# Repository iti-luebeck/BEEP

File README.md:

BEEP
====

BEEP is a small mobile robot build for education purposes.

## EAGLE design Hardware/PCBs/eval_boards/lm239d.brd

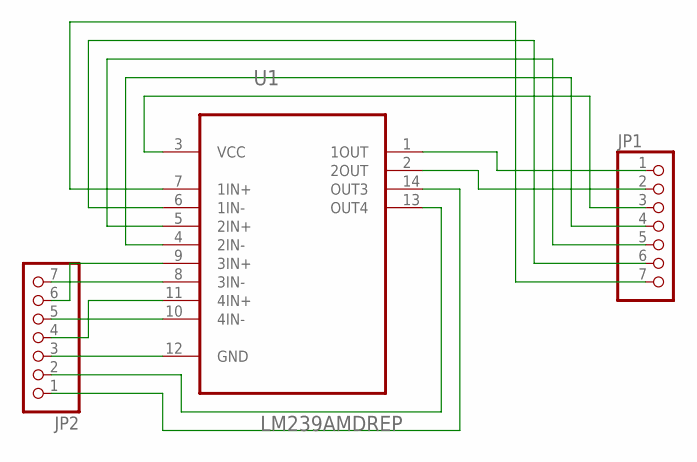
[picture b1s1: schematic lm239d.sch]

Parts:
JP1, JP2: PINHD-1X7; 1X07
U1: LM239AMDREP; SOIC127P600X175-14N

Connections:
unnamed: JP1.1, U1.1 (1OUT)
unnamed: JP1.2, U1.2 (2OUT)
unnamed: JP1.3, U1.3 (VCC)
unnamed: JP1.4, U1.4 (2IN-)
unnamed: JP1.5, U1.5 (2IN+)
unnamed: JP1.6, U1.6 (1IN-)
unnamed: JP1.7, U1.7 (1IN+)
unnamed: JP2.7, U1.8 (3IN-)
unnamed: JP2.6, U1.9 (3IN+)
unnamed: JP2.4, U1.11 (4IN+)
unnamed: JP2.5, U1.10 (4IN-)
unnamed: JP2.3, U1.12 (GND)
unnamed: JP2.2, U1.13 (OUT4)
unnamed: JP2.1, U1.14 (OUT3)

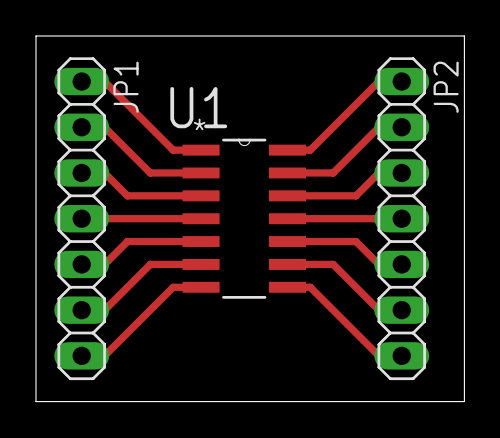
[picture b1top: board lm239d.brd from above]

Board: 2 copper layers, 23.8 x 20.3 mm, 3 parts (0 on the bottom side), 14 nets.

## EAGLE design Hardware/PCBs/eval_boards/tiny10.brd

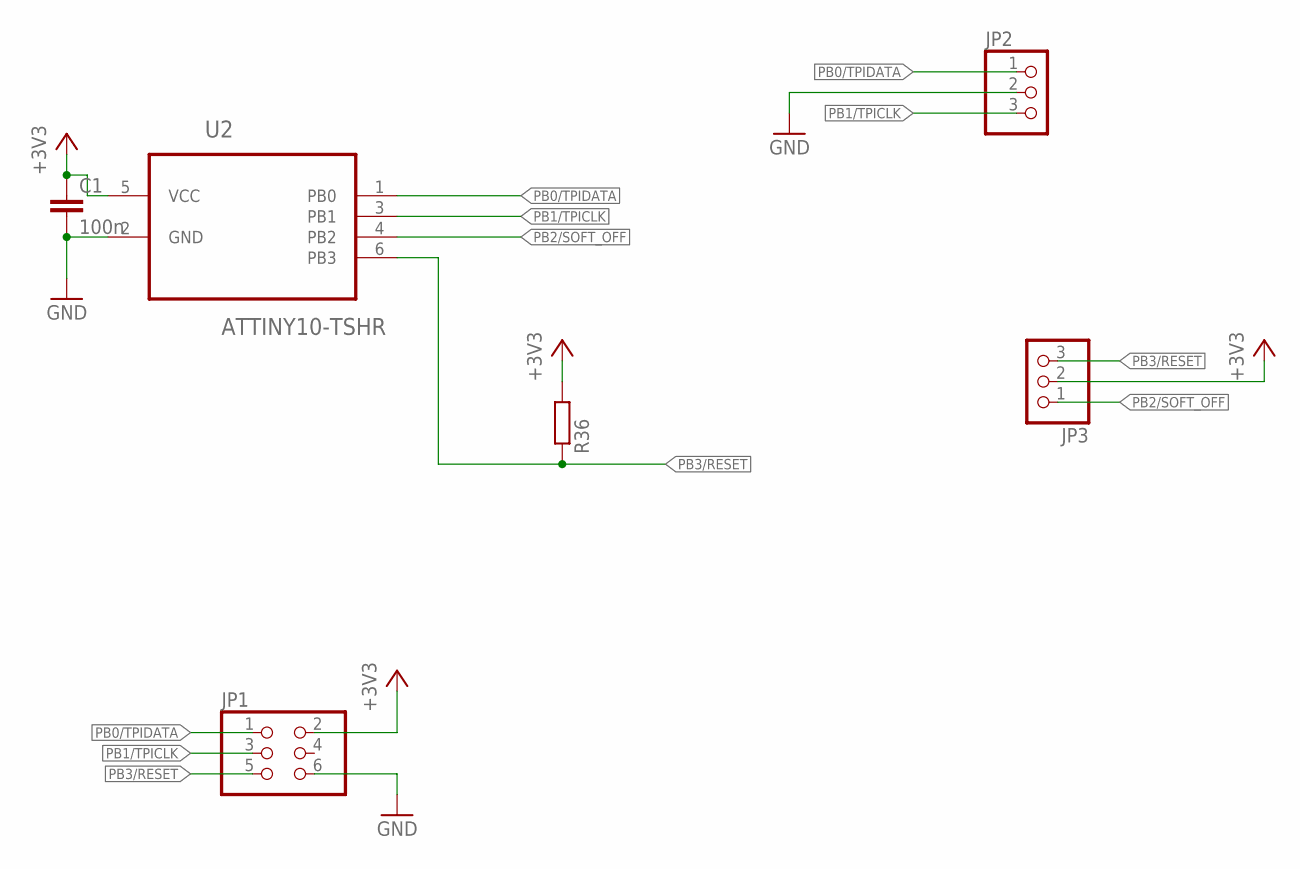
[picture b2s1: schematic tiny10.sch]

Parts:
C1: 100n; C0603
JP1: PINHD-2X3; 2X03
JP2, JP3: PINHD-1X3; 1X03
R36: R-EU_M0805; M0805
U2: ATTINY10-TSHR; SOT95P280X145-6N

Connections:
+3V3: C1.1, JP1.2, JP3.2, R36.2, U2.5 (VCC)
GND: C1.2, JP1.6, JP2.2, U2.2 (GND)
PB0/TPIDATA: JP1.1, JP2.1, U2.1 (PB0)
PB1/TPICLK: JP1.3, JP2.3, U2.3 (PB1)
PB2/SOFT_OFF: JP3.1, U2.4 (PB2)
PB3/RESET: JP1.5, JP3.3, R36.1, U2.6 (PB3)

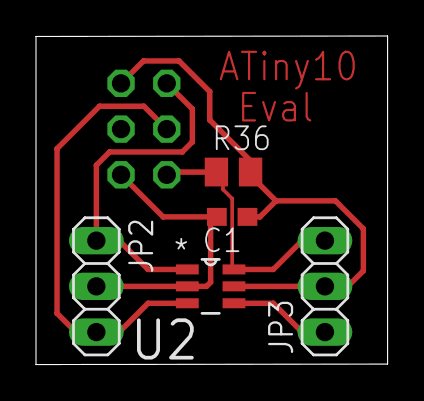
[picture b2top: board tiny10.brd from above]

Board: 2 copper layers, 19.5 x 18.3 mm, 6 parts (1 on the bottom side), 6 nets.

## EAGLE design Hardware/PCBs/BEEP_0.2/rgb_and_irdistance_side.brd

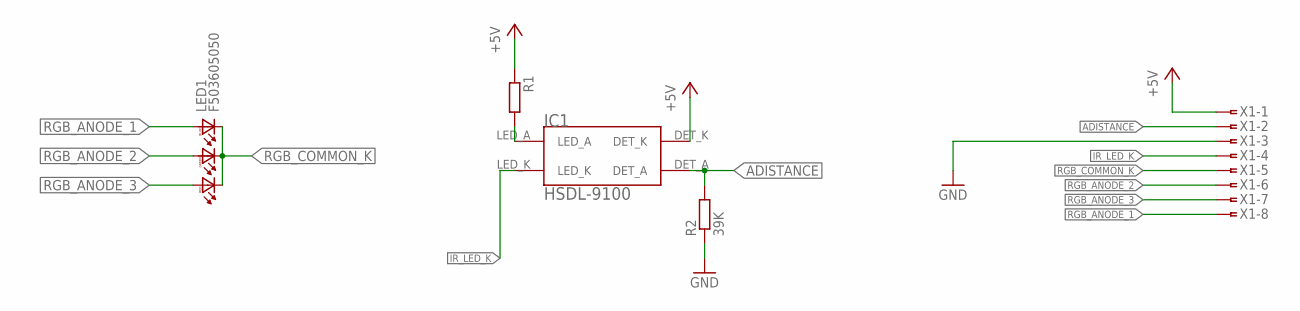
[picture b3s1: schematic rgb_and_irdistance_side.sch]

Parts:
IC1: HSDL-9100
LED1: F503605050; 5050LED
R1: R-EU_M0805; M0805
R2: 39K; M0805
X1: FTOP-8

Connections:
+5V: IC1.DET_K, R1.1, X1.1
ADISTANCE: IC1.DET_A, R2.2, X1.2
GND: R2.1, X1.3
IR_LED_K: IC1.LED_K, X1.4
unnamed: IC1.LED_A, R1.2
RGB_ANODE_1: LED1.B1 (BA), X1.8
RGB_ANODE_2: LED1.G1 (GA), X1.6
RGB_ANODE_3: LED1.R1 (RA), X1.7
RGB_COMMON_K: LED1.B2 (BC), LED1.G2 (GC), LED1.R2 (RC), X1.5

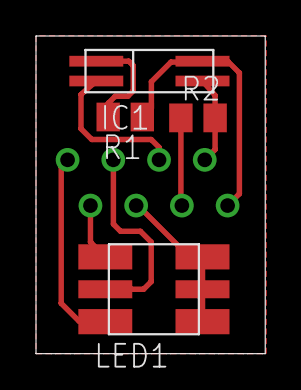
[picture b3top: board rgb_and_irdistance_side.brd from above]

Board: 2 copper layers, 12.7 x 17.7 mm, 5 parts (1 on the bottom side), 9 nets.

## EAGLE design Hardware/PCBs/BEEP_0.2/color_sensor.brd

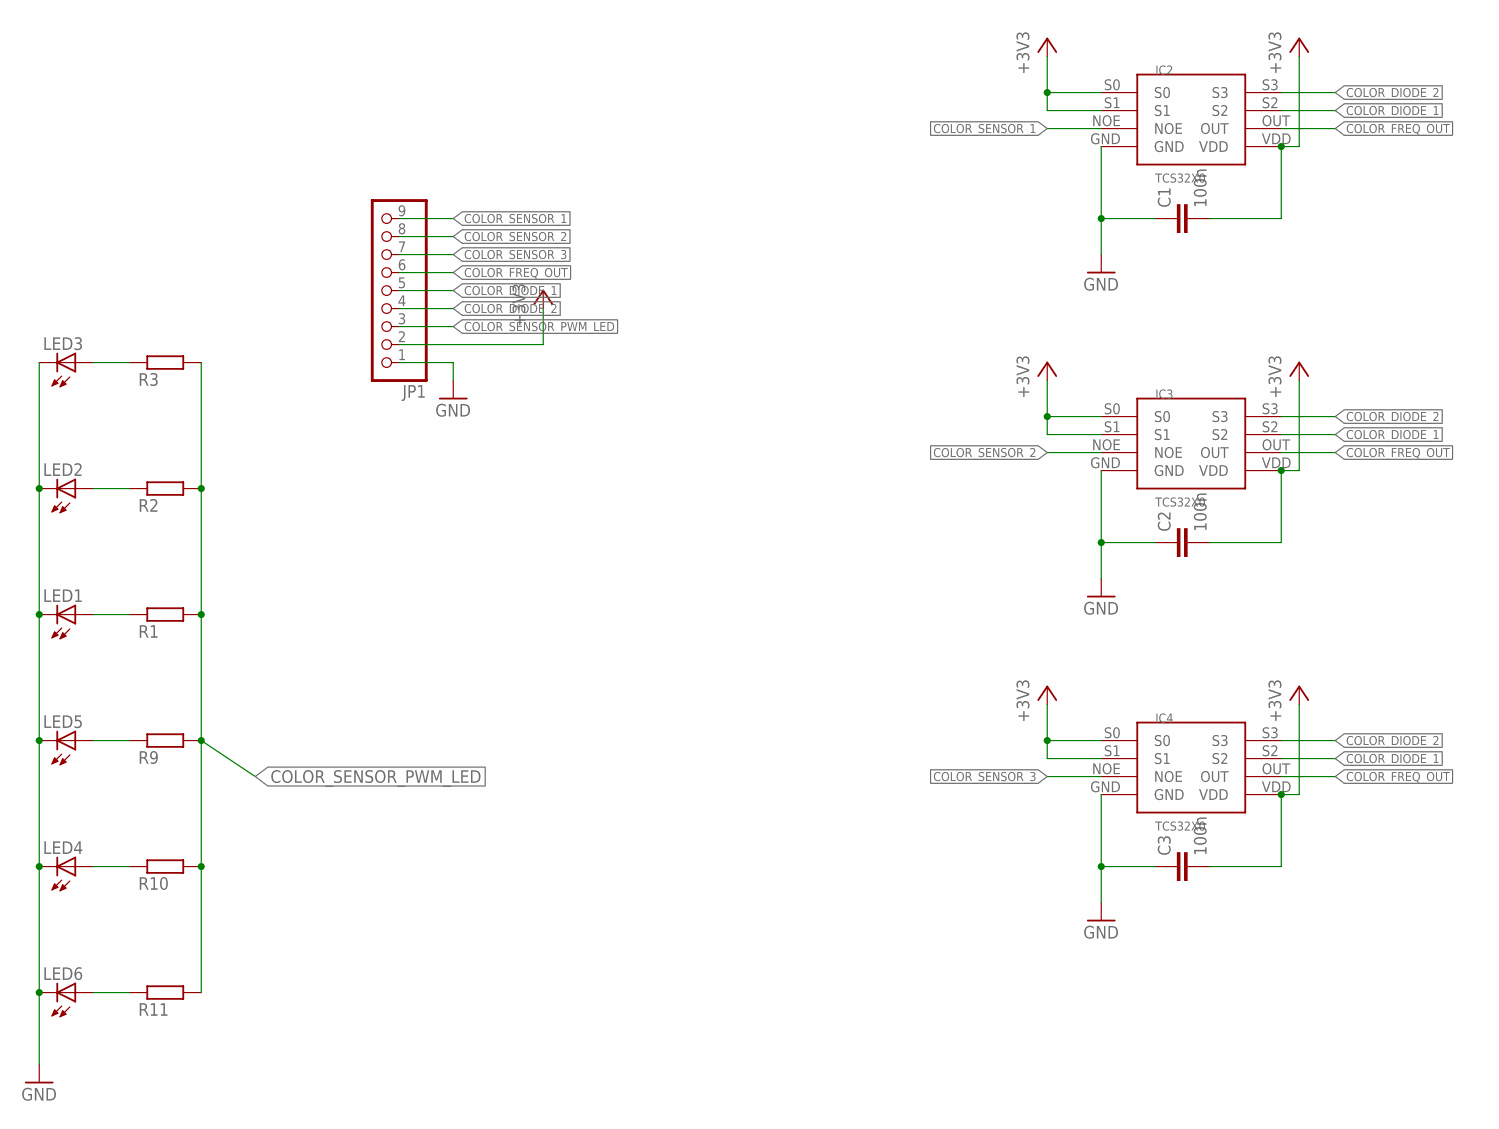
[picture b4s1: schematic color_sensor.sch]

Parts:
C1, C2, C3: 100n; C0805
IC2, IC3, IC4: TCS32X0
JP1: PINHD-1X9; 1X09
LED1, LED2, LED3, LED4, LED5, LED6: NFSG036BT
R1, R2, R3, R9, R10, R11: R-EU_M0805; M0805

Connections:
+3V3: C1.2, C2.2, C3.2, IC2.S0, IC2.S1, IC2.VDD, IC3.S0, IC3.S1, IC3.VDD, IC4.S0, IC4.S1, IC4.VDD, JP1.2
COLOR_DIODE_1: IC2.S2, IC3.S2, IC4.S2, JP1.5
COLOR_DIODE_2: IC2.S3, IC3.S3, IC4.S3, JP1.4
COLOR_FREQ_OUT: IC2.OUT, IC3.OUT, IC4.OUT, JP1.6
COLOR_SENSOR_1: IC2.NOE, JP1.9
COLOR_SENSOR_2: IC3.NOE, JP1.8
COLOR_SENSOR_3: IC4.NOE, JP1.7
COLOR_SENSOR_PWM_LED: JP1.3, R1.2, R2.2, R3.2, R9.2, R10.2, R11.2
GND: C1.1, C2.1, C3.1, IC2.GND, IC3.GND, IC4.GND, JP1.1, LED1.C, LED2.C, LED3.C, LED4.C, LED5.C, LED6.C
unnamed: LED1.A, R1.1
unnamed: LED2.A, R2.1
unnamed: LED3.A, R3.1
unnamed: LED5.A, R9.1
unnamed: LED4.A, R10.1
unnamed: LED6.A, R11.1

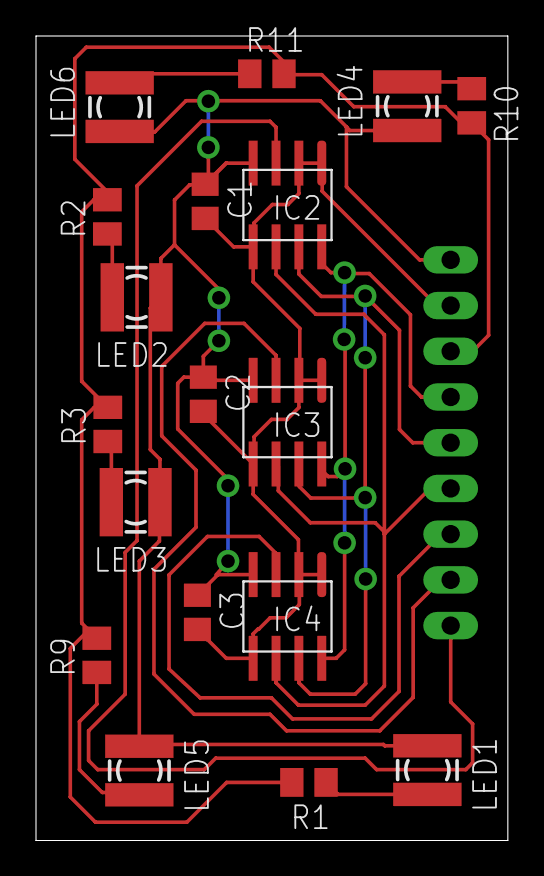
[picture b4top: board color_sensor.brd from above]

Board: 2 copper layers, 26.2 x 44.7 mm, 19 parts (1 on the bottom side), 15 nets.

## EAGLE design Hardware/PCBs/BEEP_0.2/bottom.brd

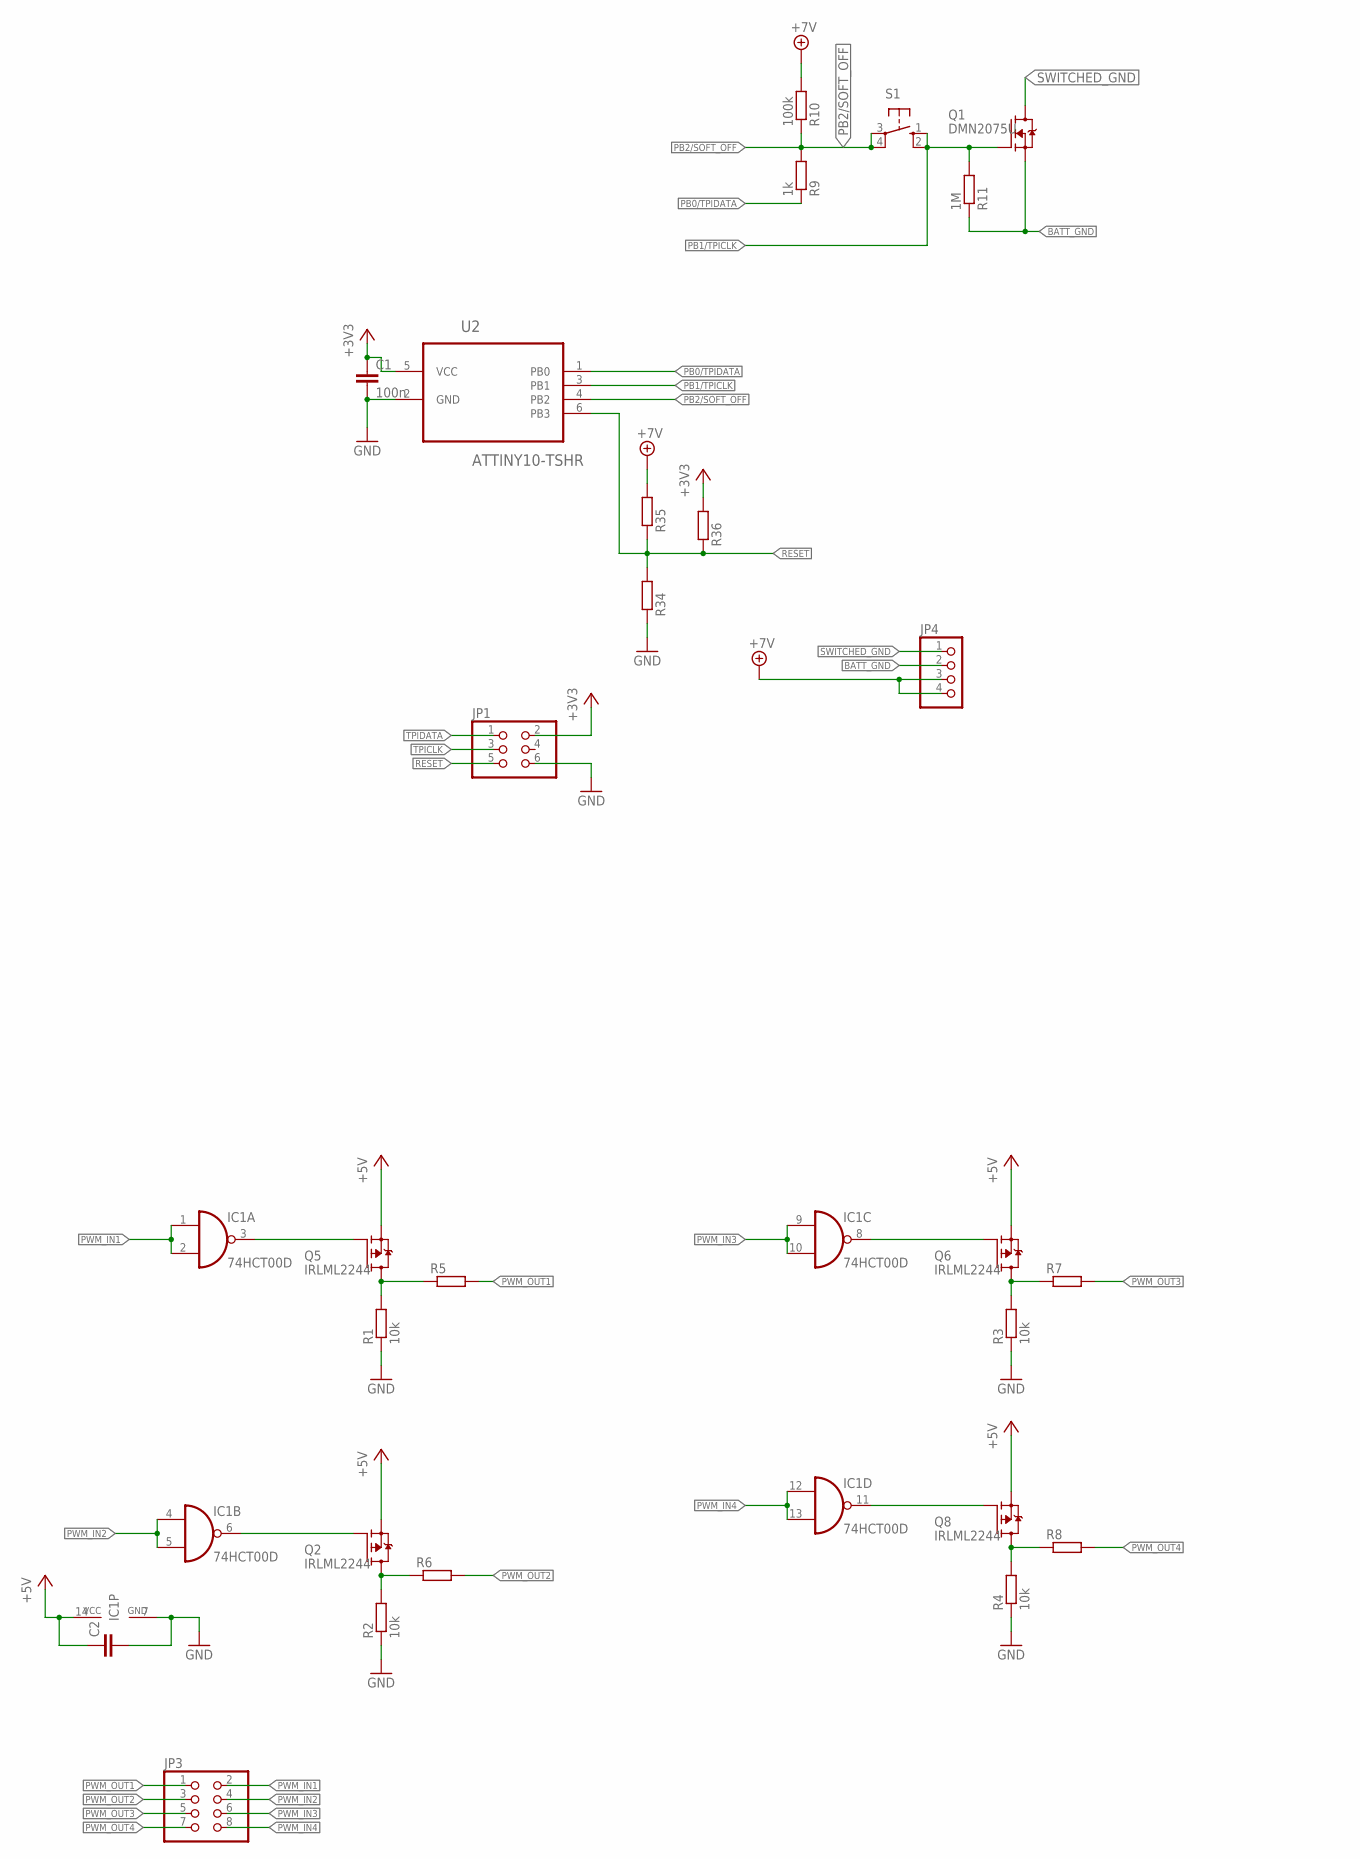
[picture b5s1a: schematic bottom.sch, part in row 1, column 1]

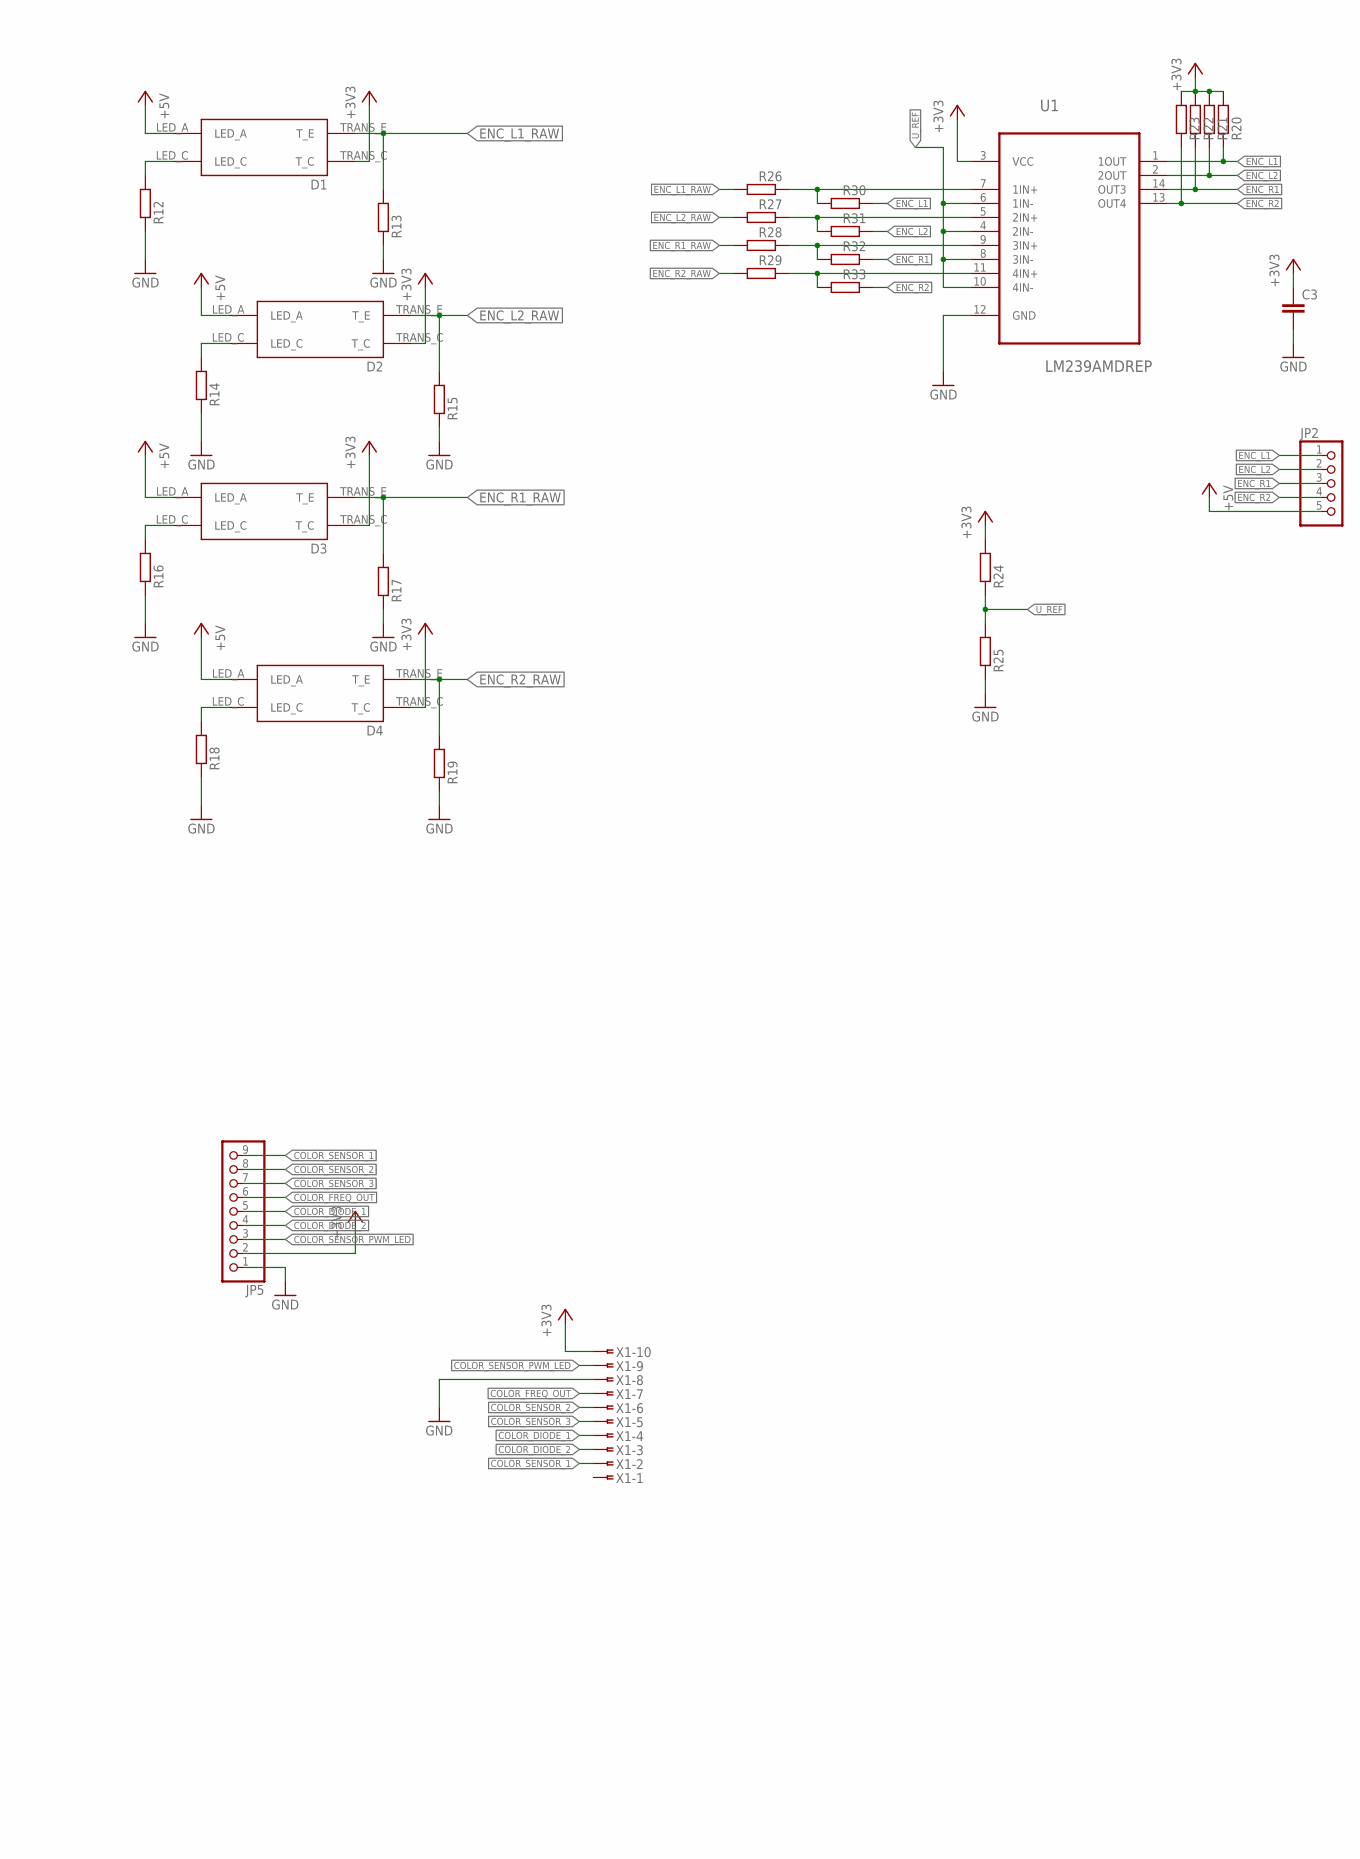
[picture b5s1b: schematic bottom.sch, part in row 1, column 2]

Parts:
C1: 100n; C0603
C2, C3: C-EUC0603; C0603
D1, D2, D3, D4: CNY70
IC1: 74HCT00D; SO14
JP1: PINHD-2X3; 2X03
JP2: PINHD-1X5; 1X05
JP3: PINHD-2X4; 2X04
JP4: PINHD-1X4; 1X04
JP5: PINHD-1X9; 1X09
Q1: DMN2075U; SOT95P240X112-3N
Q2, Q5, Q6, Q8: IRLML2244; SOT95P240X112-3N
R1, R2, R3, R4: 10k; R0603
R5, R6, R7, R8, R13, R14, R15, R16, R17, R18, R19, R20, R21, R22, R23, R24, R25, R26, R27, R28, R29, R30, R31, R32, R33, R34, R35, R36: R-EU_M0805; M0805
R9: 1k; M0805
R10: 100k; M0805
R11: 1M; M0805
R12: R-EU_R0805; R0805
S1: 10-XX; B3F-10XX
U1: LM239AMDREP; SOIC127P600X175-14N
U2: ATTINY10-TSHR; SOT95P280X145-6N
X1: FTOP-10

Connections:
+3V3: C1.1, C3.1, D1.TRANS_C (T_C), D2.TRANS_C (T_C), D3.TRANS_C (T_C), D4.TRANS_C (T_C), JP1.2, JP5.2, R20.2, R21.2, R22.2, R23.2, R24.2, R36.2, U1.3 (VCC), U2.5 (VCC), X1.10
+5V: C2.1, D1.LED_A, D2.LED_A, D3.LED_A, D4.LED_A, IC1.14 (VCC), JP2.5, Q2.S, Q5.S, Q6.S, Q8.S
+7V: JP4.3, JP4.4, R10.2, R35.2
BATT_GND: JP4.2, Q1.S, R11.1
COLOR_DIODE_1: JP5.5, X1.4
COLOR_DIODE_2: JP5.4, X1.3
COLOR_FREQ_OUT: JP5.6, X1.7
COLOR_SENSOR_1: JP5.9, X1.2
COLOR_SENSOR_2: JP5.8, X1.6
COLOR_SENSOR_3: JP5.7, X1.5
COLOR_SENSOR_PWM_LED: JP5.3, X1.9
ENC_L1: JP2.1, R20.1, R30.1, U1.1 (1OUT)
ENC_L1_RAW: D1.TRANS_E (T_E), R13.2, R26.2
ENC_L2: JP2.2, R21.1, R31.1, U1.2 (2OUT)
ENC_L2_RAW: D2.TRANS_E (T_E), R15.2, R27.2
ENC_R1: JP2.3, R22.1, R32.1, U1.14 (OUT3)
ENC_R1_RAW: D3.TRANS_E (T_E), R17.2, R28.2
ENC_R2: JP2.4, R23.1, R33.1, U1.13 (OUT4)
ENC_R2_RAW: D4.TRANS_E (T_E), R19.2, R29.2
GND: C1.2, C2.2, C3.2, IC1.7 (GND), JP1.6, JP5.1, R1.1, R2.1, R3.1, R4.1, R12.1, R13.1, R14.1, R15.1, R16.1, R17.1, R18.1, R19.1, R25.1, R34.1, U1.12 (GND), U2.2 (GND), X1.8
unnamed: IC1.3 (O), Q5.G
unnamed: IC1.6 (O), Q2.G
unnamed: Q5.D, R1.2, R5.1
unnamed: IC1.8 (O), Q6.G
unnamed: IC1.11 (O), Q8.G
unnamed: Q8.D, R4.2, R8.1
unnamed: Q6.D, R3.2, R7.1
unnamed: Q2.D, R2.2, R6.1
unnamed: D1.LED_C, R12.2
unnamed: R26.1, R30.2, U1.7 (1IN+)
unnamed: R27.1, R31.2, U1.5 (2IN+)
unnamed: D2.LED_C, R14.2
unnamed: R28.1, R32.2, U1.9 (3IN+)
unnamed: D3.LED_C, R16.2
unnamed: R29.1, R33.2, U1.11 (4IN+)
unnamed: D4.LED_C, R18.2
PB0/TPIDATA: R9.1, U2.1 (PB0)
PB1/TPICLK: Q1.G, R11.2, S1.1 (S), S1.2 (S1), U2.3 (PB1)
PB2/SOFT_OFF: R9.2, R10.1, S1.3, S1.4 (P1), U2.4 (PB2)
PWM_IN1: IC1.1 (I0), IC1.2 (I1), JP3.2
PWM_IN2: IC1.4 (I0), IC1.5 (I1), JP3.4
PWM_IN3: IC1.9 (I0), IC1.10 (I1), JP3.6
PWM_IN4: IC1.12 (I0), IC1.13 (I1), JP3.8
PWM_OUT1: JP3.1, R5.2
PWM_OUT2: JP3.3, R6.2
PWM_OUT3: JP3.5, R7.2
PWM_OUT4: JP3.7, R8.2
RESET: JP1.5, R34.2, R35.1, R36.1, U2.6 (PB3)
SWITCHED_GND: JP4.1, Q1.D
TPICLK: JP1.3
TPIDATA: JP1.1
U_REF: R24.1, R25.2, U1.4 (2IN-), U1.6 (1IN-), U1.8 (3IN-), U1.10 (4IN-)

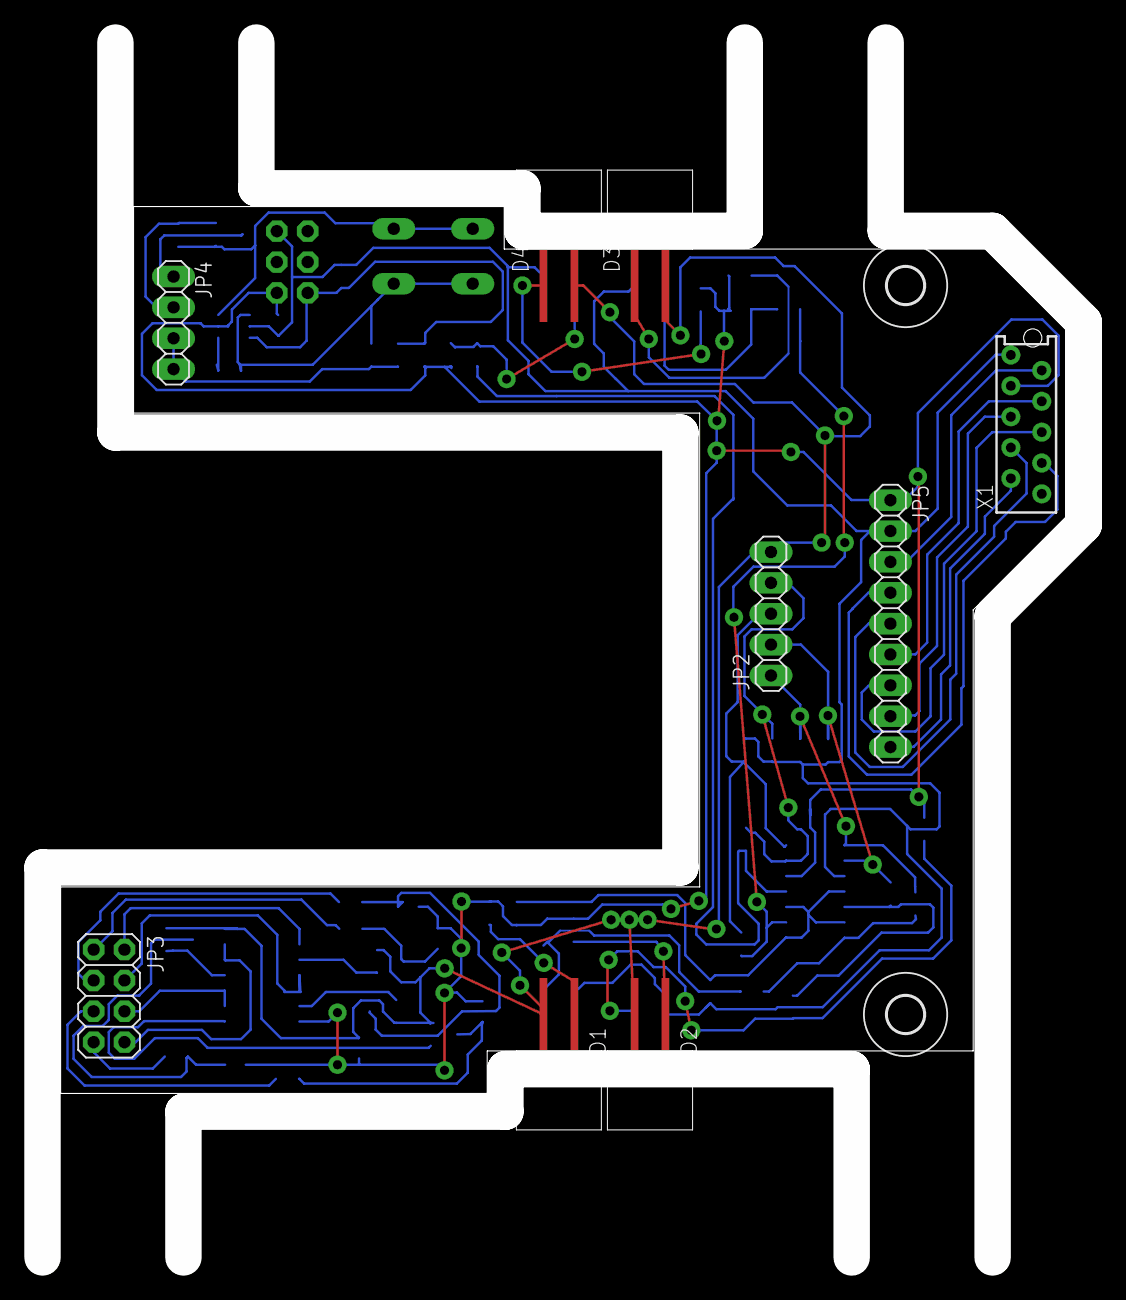
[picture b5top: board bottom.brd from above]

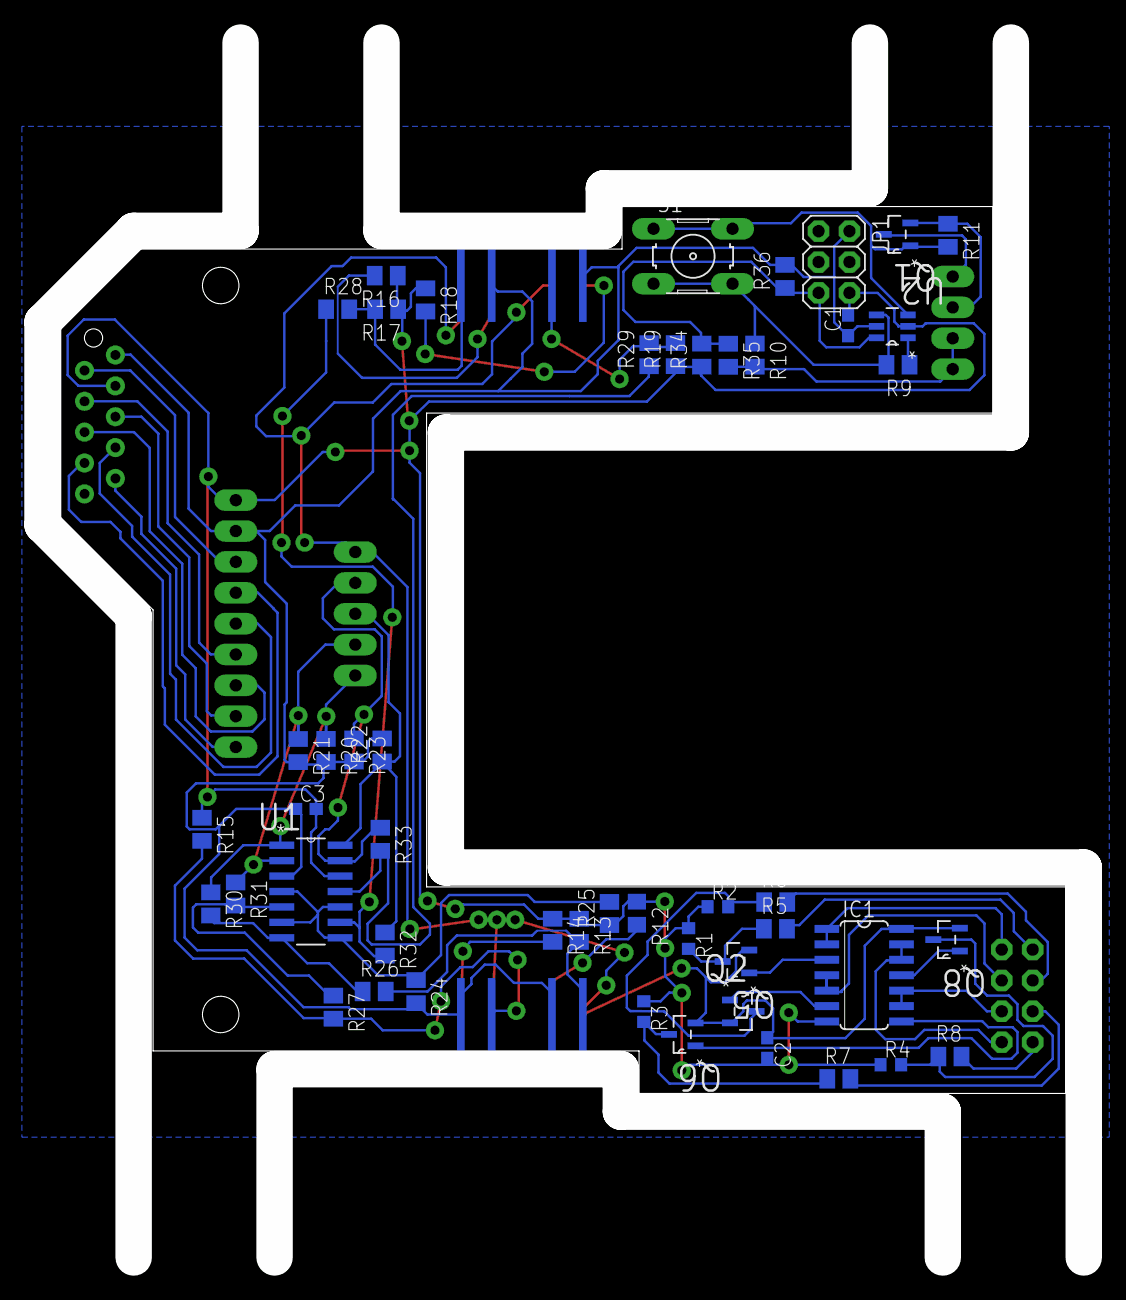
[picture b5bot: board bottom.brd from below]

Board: 2 copper layers, 85.7 x 100.0 mm, 60 parts (49 on the bottom side), 50 nets.

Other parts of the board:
U$1, U$2: 3,0

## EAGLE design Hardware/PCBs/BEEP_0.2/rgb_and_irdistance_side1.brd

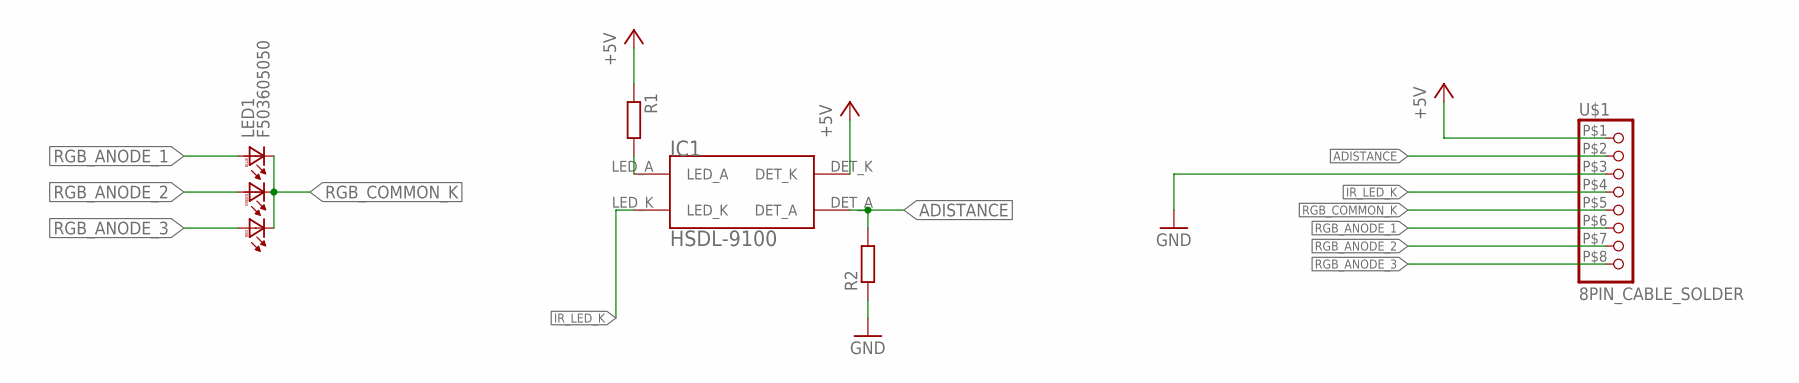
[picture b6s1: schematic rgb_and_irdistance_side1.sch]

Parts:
IC1: HSDL-9100
LED1: F503605050; 5050LED
R1, R2: R-EU_M0805; M0805
U$1: 8PIN_CABLE_SOLDER

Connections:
+5V: IC1.DET_K, R1.1, U$1.P$1 (1)
ADISTANCE: IC1.DET_A, R2.2, U$1.P$2 (2)
GND: R2.1, U$1.P$3 (3)
IR_LED_K: IC1.LED_K, U$1.P$4 (4)
unnamed: IC1.LED_A, R1.2
RGB_ANODE_1: LED1.B1 (BA), U$1.P$6 (6)
RGB_ANODE_2: LED1.G1 (GA), U$1.P$7 (7)
RGB_ANODE_3: LED1.R1 (RA), U$1.P$8 (8)
RGB_COMMON_K: LED1.B2 (BC), LED1.G2 (GC), LED1.R2 (RC), U$1.P$5 (5)

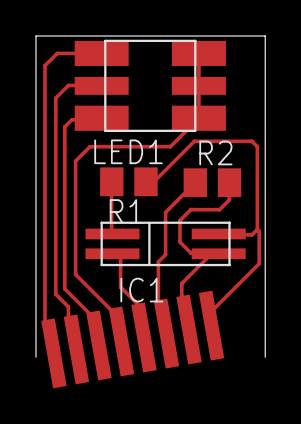
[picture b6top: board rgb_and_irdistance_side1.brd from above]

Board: 2 copper layers, 12.7 x 17.9 mm, 5 parts (0 on the bottom side), 9 nets.

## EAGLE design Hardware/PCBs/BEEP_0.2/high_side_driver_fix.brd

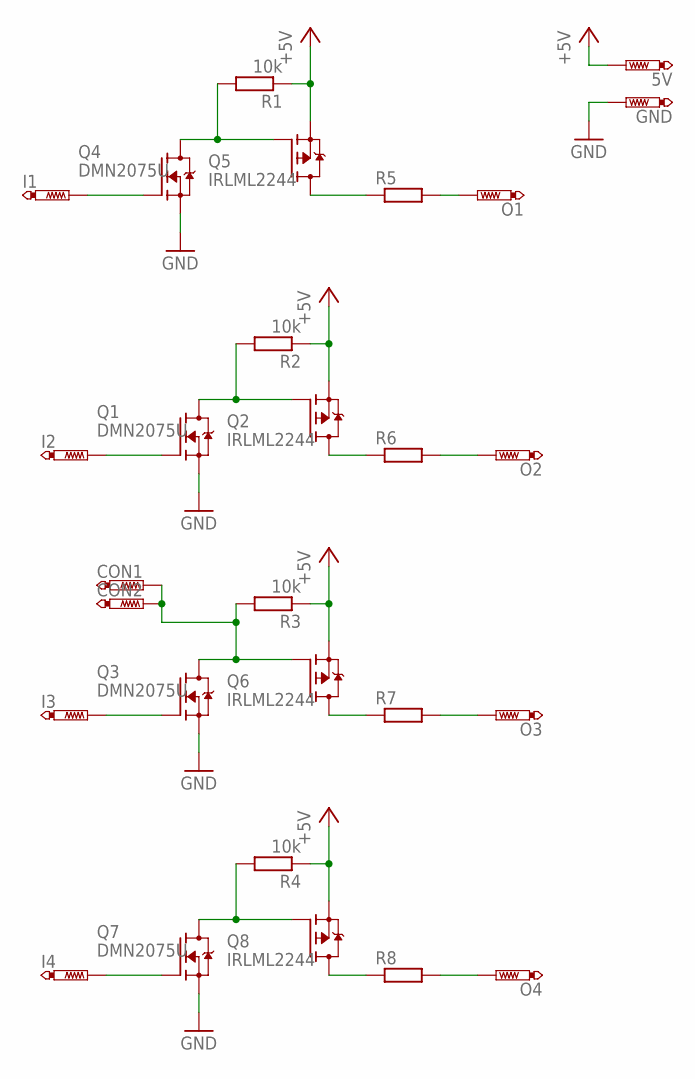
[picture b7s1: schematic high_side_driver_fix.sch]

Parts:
5V: PTR1TP11SQ; TP11SQ
CON1, CON2: PTR1TP08SQ; TP08SQ
GND: PTR1TP11SQ; TP11SQ
I1, I2, I3, I4: PTR1TP11SQ; TP11SQ
O1, O2, O3, O4: PTR1TP11SQ; TP11SQ
Q1, Q3, Q4, Q7: DMN2075U; SOT95P240X112-3N
Q2, Q5, Q6, Q8: IRLML2244; SOT95P240X112-3N
R1, R2, R3, R4: 10k; R0603
R5, R6, R7, R8: R-EU_M0805; M0805

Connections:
+5V: 5V.TP, Q2.S, Q5.S, Q6.S, Q8.S, R1.1, R2.1, R3.1, R4.1
GND: GND.TP, Q1.S, Q3.S, Q4.S, Q7.S
unnamed: Q4.D, Q5.G, R1.2
unnamed: I1.TP, Q4.G
unnamed: Q5.D, R5.1
unnamed: Q1.D, Q2.G, R2.2
unnamed: I2.TP, Q1.G
unnamed: O2.TP, R6.2
unnamed: CON1.TP, CON2.TP, Q3.D, Q6.G, R3.2
unnamed: I3.TP, Q3.G
unnamed: O3.TP, R7.2
unnamed: Q7.D, Q8.G, R4.2
unnamed: I4.TP, Q7.G
unnamed: O4.TP, R8.2
unnamed: Q8.D, R8.1
unnamed: Q6.D, R7.1
unnamed: Q2.D, R6.1
unnamed: O1.TP, R5.2

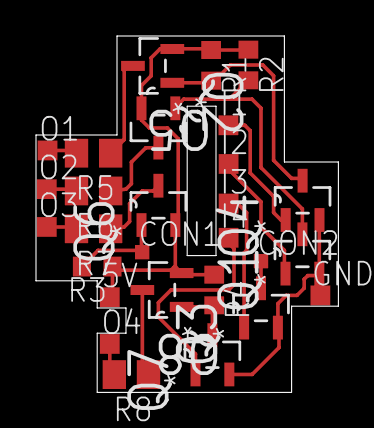
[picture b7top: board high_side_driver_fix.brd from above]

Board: 2 copper layers, 16.8 x 19.8 mm, 28 parts (0 on the bottom side), 18 nets.

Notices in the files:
parts and their libraries:
SparkFun-PowerIC: Licensing: CC v3.0 Share-Alike You are welcome to use this library for commercial purposes.
